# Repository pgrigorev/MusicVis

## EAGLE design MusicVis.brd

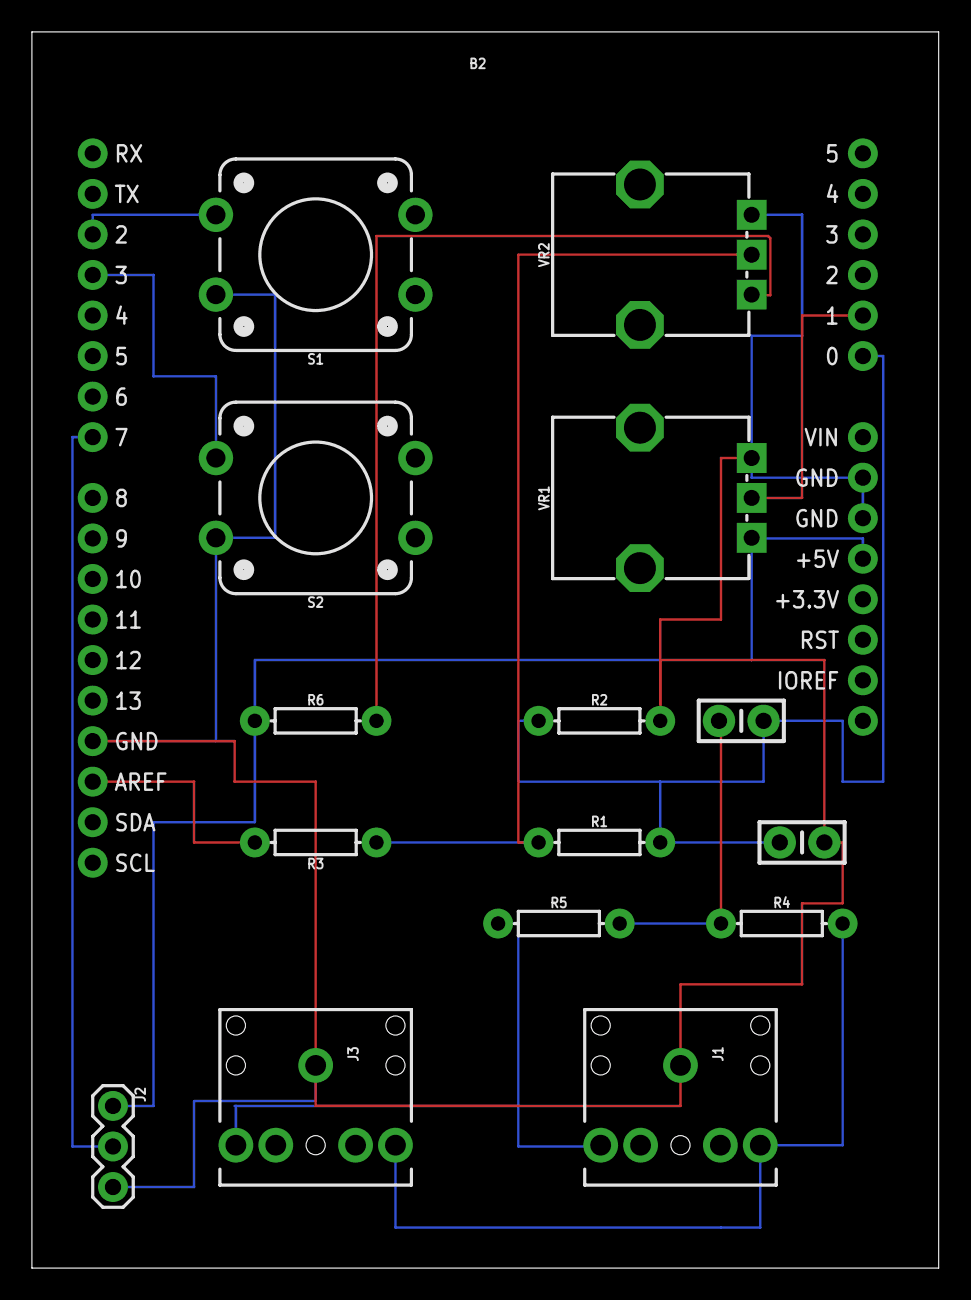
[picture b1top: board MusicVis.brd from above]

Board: 2 copper layers, 56.8 x 77.5 mm, 16 parts (0 on the bottom side), 13 nets.

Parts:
B2: ARDUINO_UNO_R3_SHIELDBASIC; UNO_R3_SHIELD
C1, C2: 0.1uF; CAP-PTH-SMALL-KIT
J1, J3: AUDIO_JACK_3.5MM_PTH; AUDIO-JACK
J2: 455-1750-1-ND; 1X03
R1, R2: 100k; AXIAL-0.3
R3, R4, R5, R6: 1k; AXIAL-0.3
S1, S2: MOMENTARY-SWITCH-SPST-PTH-12MM; TACTILE_SWITCH_PTH_12MM
VR1, VR2: 10k; POT-PTH-ALPS

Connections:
5V: B2.5V, J2.1, R6.P$1, VR1.P$1
GND: B2.GND@0, B2.GND@1, B2.GND@2, C1.2, J1.SLEEVE, J2.3, J3.SLEEVE, R2.P$2, S1.3, S2.3, VR1.P$3, VR2.P$3
unnamed: B2.D2, S1.1
unnamed: B2.D3, S2.1
unnamed: B2.D7, J2.2
unnamed: J1.TIP, J3.TIP, R5.P$1
unnamed: J1.RING, J3.RING, R4.P$2
unnamed: C2.1, R4.P$1, R5.P$2
unnamed: R6.P$2, VR2.P$1
unnamed: B2.A0, C1.1, C2.2, R1.P$2, R2.P$1
unnamed: B2.AREF, R3.P$2
unnamed: R1.P$1, R3.P$1, VR2.P$2
unnamed: B2.A1, VR1.P$2

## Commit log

2018-03-04 First pcd layout
2018-03-04 Second draft of the board with pth elements and hand made connections
2018-03-05 add origunal scheme as png

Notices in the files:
parts and their libraries:
SparkFun-Boards: Licensing: Creative Commons ShareAlike 4.0 International - https://creativecommons.org/licenses/by-sa/4.0
